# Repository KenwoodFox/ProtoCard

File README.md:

# References

It does look pretty sick though

https://youtu.be/Xo8rYATKyDA

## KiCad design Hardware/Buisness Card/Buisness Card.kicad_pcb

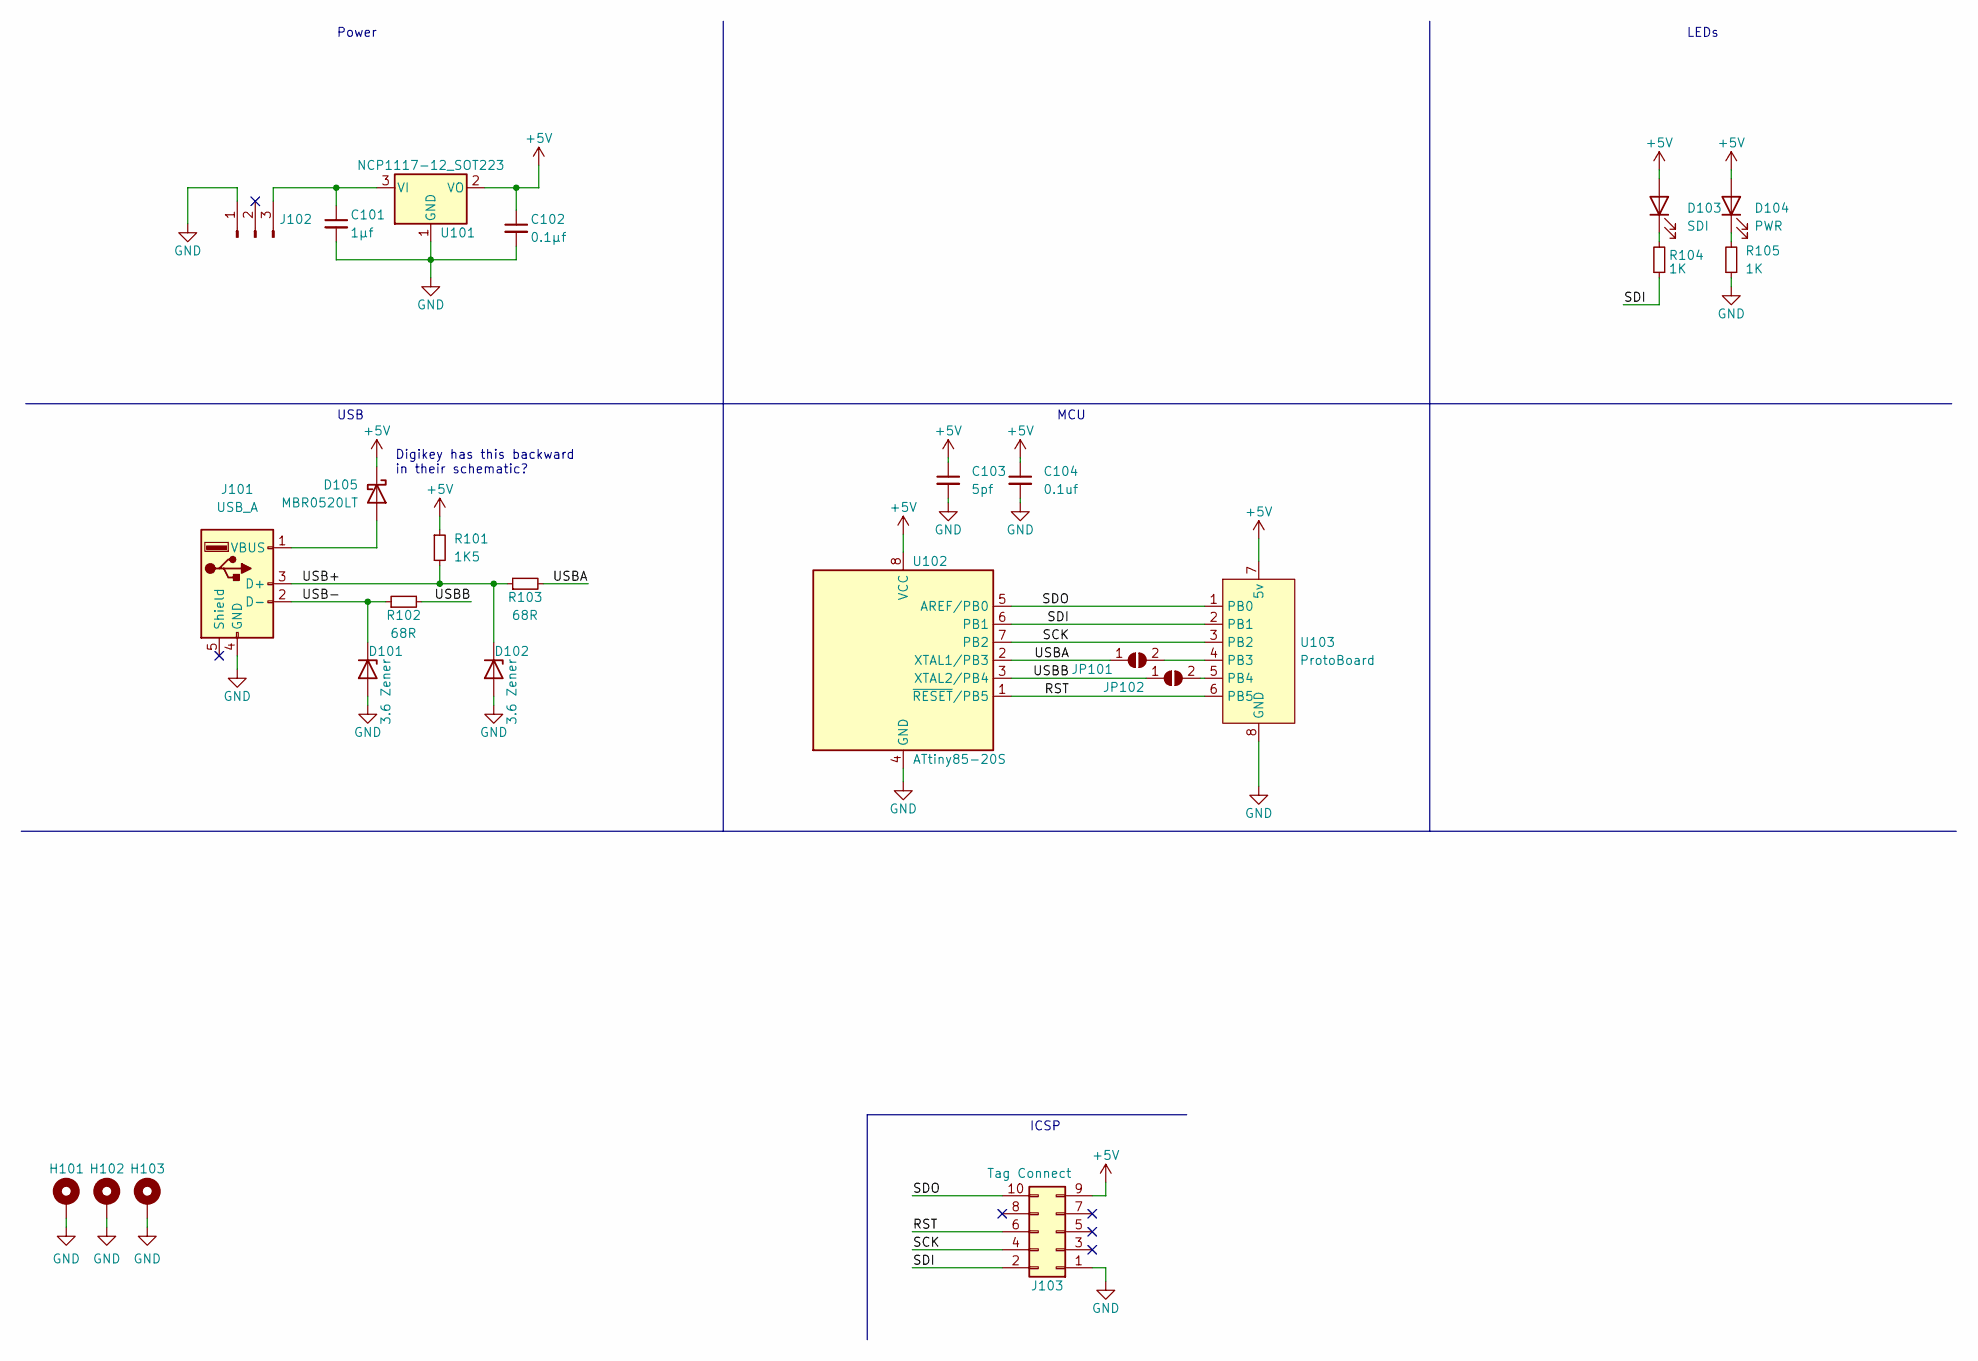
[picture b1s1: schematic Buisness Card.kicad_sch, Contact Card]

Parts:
C101: 1μf; C_0805_2012Metric; LCSC# C28323
C102: 0.1μf; C_0805_2012Metric; LCSC# C138340
C103: 5pf; C_0805_2012Metric; LCSC# C1824
C104: 0.1uf; C_0805_2012Metric; LCSC# C138340
D101, D102: 3.6 Zener; D_0805_2012Metric; LCSC# C2891771
D103: SDI; LED_0805_2012Metric; LCSC# C84256
D104: PWR; LED_0805_2012Metric; LCSC# C84256
D105: MBR0520LT; D_SOD-123; LCSC# C165467
H101, H102, H103: MountingHole_Pad; MountingHole_2.2mm_M2_Pad
J101: USB_A; usb-PCB
J102: Conn_01x03_Male; PinHeader_1x03_P2.54mm_Vertical
J103: Tag Connect; Tag-Connect_TC2050-IDC-FP_2x05_P1.27mm_Vertical
JP101, JP102: SolderJumper_2_Open; SolderJumper-2_P1.3mm_Open_Pad1.0x1.5mm
R101: 1K5; R_0805_2012Metric; LCSC# C325846
R102, R103: 68R; R_0805_2012Metric; LCSC# C17802
R104, R105: 1K; R_0805_2012Metric; LCSC# C17513
U101: NCP1117-12_SOT223; SOT-223-3_TabPin2
U102: ATtiny85-20S; SOIC-8W_5.3x5.3mm_P1.27mm; LCSC# C89852
U103: ProtoBoard; ProtoBoardLayout

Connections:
+5V: C102.1, C103.1, C104.1, D103.2 (A), D104.2 (A), D105.1 (K), J103.9, R101.1, U101.2 (VO), U102.8 (VCC), U103.7 (5v)
/RST: J103.6, U102.1 (~RESET/PB5), U103.6 (PB5)
/SCK: J103.4, U102.7 (PB2), U103.3 (PB2)
/SDI: J103.2, R104.1, U102.6 (PB1), U103.2 (PB1)
/SDO: J103.10, U102.5 (AREF/PB0), U103.1 (PB0)
/USB+: D102.1 (K), J101.3 (D+), R101.2, R103.1
/USB-: D101.1 (K), J101.2 (D-), R102.1
/USBA: JP101.1 (A), R103.2, U102.2 (XTAL1/PB3)
/USBB: JP102.1 (A), R102.2, U102.3 (XTAL2/PB4)
GND: C101.2, C102.2, C103.2, C104.2, D101.2 (A), D102.2 (A), H101.1, H102.1, H103.1, J101.4 (GND), J102.1, J103.1, R105.1, U101.1 (GND), U102.4 (GND), U103.8 (GND)
unnamed: C101.1, J102.3, U101.3 (VI)
unnamed: D103.1 (K), R104.2
unnamed: D104.1 (K), R105.2
unnamed: D105.2 (A), J101.1 (VBUS)
unnamed: JP101.2 (B), U103.4 (PB3)
unnamed: JP102.2 (B), U103.5 (PB4)

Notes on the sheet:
Power
USB
LEDs
MCU
ICSP
Digikey has this backward in their schematic?

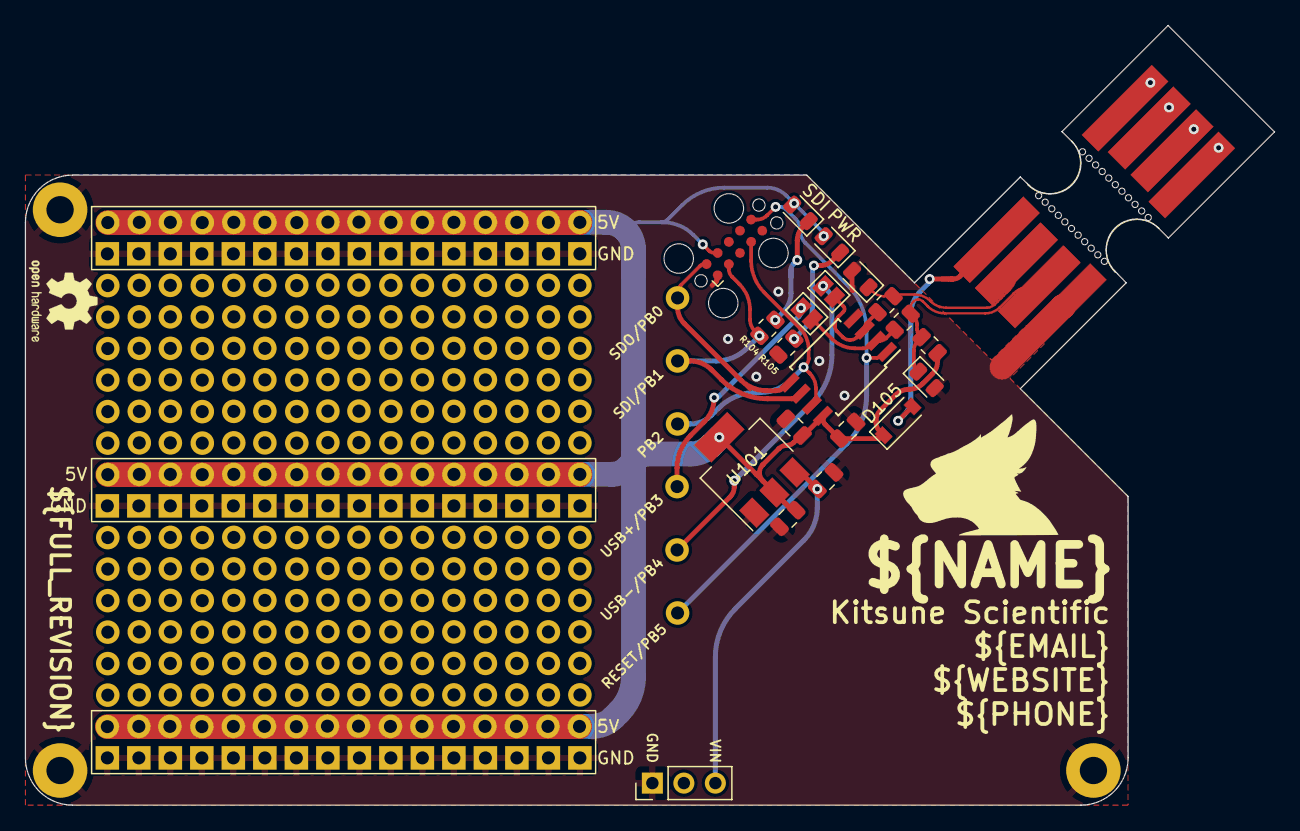
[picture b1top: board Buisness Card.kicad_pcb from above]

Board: 2 copper layers, 100.7 x 62.9 mm, 28 parts (1 on the bottom side), 16 nets.

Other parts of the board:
P1, P1#2: USB_A; usb-PCB
mouse-bite-5mm-slot: VAL**; mouse-bite-5mm-slot

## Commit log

2022-08-10 Init to commit it
2022-08-11 Change a few things maybe:
2022-08-12 put diode in the right way
2022-08-16 Update a few things
2022-08-16 Bump ver
2022-09-18 Start to make changes for a sleeker design
2022-10-08 Perform a lot of extra rework for a v.2
2022-10-08 Add in blanking text vars
2022-10-08 Include revision tag next to jlc number
2022-10-08 U8GLIB
2022-10-08 Add adafruit
2022-10-16 Added submodule for micronucleus firmware
2023-06-03 Bump and make curvy
2023-06-03 Slap some CI on there
2023-06-13 Prep for new order
2023-06-13 Fix firmware
2023-06-13 Fix hardware
2023-06-13 Clean hw names and prepare to squash
2023-06-13 Add qoutes
2023-06-13 Remove junk
2023-06-13 Clean PCB
2023-06-13 V2.0 Design (#1)
2023-06-13 Add stencil dimensions
2023-06-24 Add stencil cad
2023-06-24 Fix for #2
2023-06-24 Fix 3d model too
2023-06-24 Fix for #2 (#3)
2023-06-24 bump stencil
2023-06-24 Add stencil cutouts for usb
2023-06-28 Add missing holes
